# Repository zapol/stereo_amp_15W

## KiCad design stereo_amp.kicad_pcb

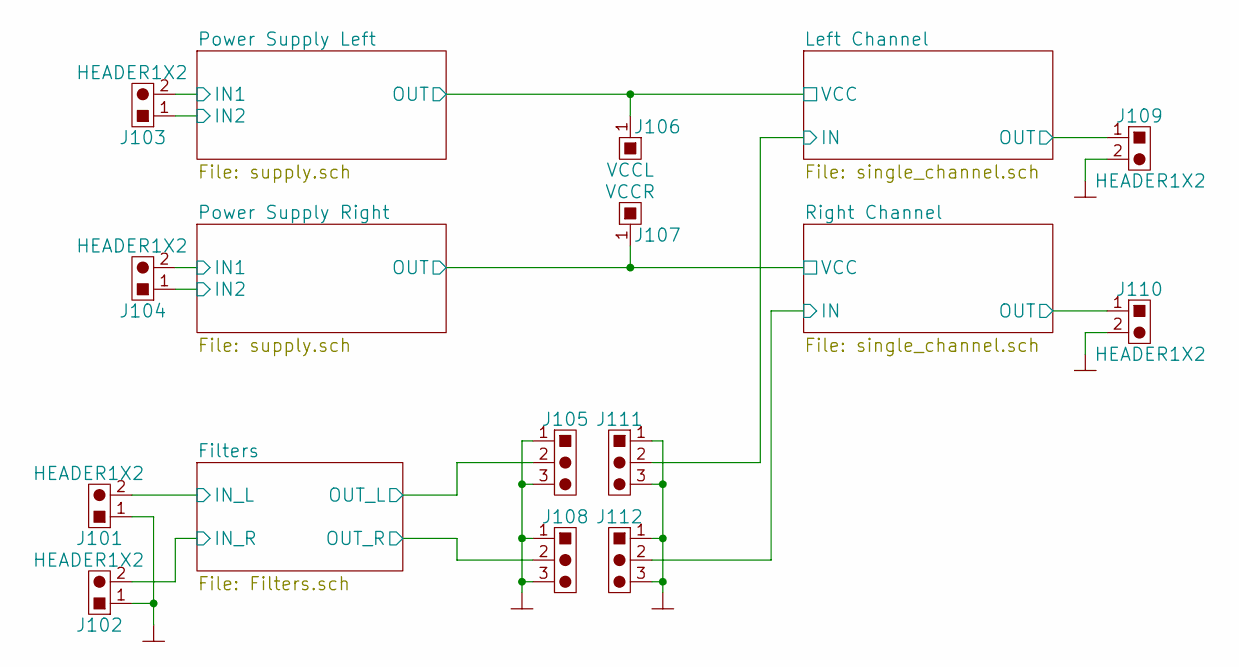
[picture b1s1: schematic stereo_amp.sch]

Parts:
J101, J102: HEADER1X2; HEADER1x2V
J103, J104, J109, J110: HEADER1X2; STL1550%2f2-GH
J105, J108, J111, J112: HEADER1X3; HEADER1x3V
J106: VCCL; MountHole_D4P6
J107: VCCR; MountHole_D4P6

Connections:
/Filters/IN_L: J101.2; also elsewhere on the board
/Filters/IN_R: J102.2; also elsewhere on the board
/Filters/OUT_L: J105.2; also elsewhere on the board
/Filters/OUT_R: J108.2; also elsewhere on the board
/Left Channel/IN: J111.2; also elsewhere on the board
/Left Channel/OUT: J109.1; also elsewhere on the board
/Power Supply Left/IN1: J103.2; also elsewhere on the board
/Power Supply Left/IN2: J103.1; also elsewhere on the board
/Power Supply Left/OUT: J106.1; also elsewhere on the board
/Power Supply Right/IN1: J104.2; also elsewhere on the board
/Power Supply Right/IN2: J104.1; also elsewhere on the board
/Power Supply Right/OUT: J107.1; also elsewhere on the board
/Right Channel/IN: J112.2; also elsewhere on the board
/Right Channel/OUT: J110.1; also elsewhere on the board
GND: J101.1, J102.1, J105.1, J105.3, J108.1, J108.3, J109.2, J110.2, J111.1, J111.3, J112.1, J112.3; also elsewhere on the board

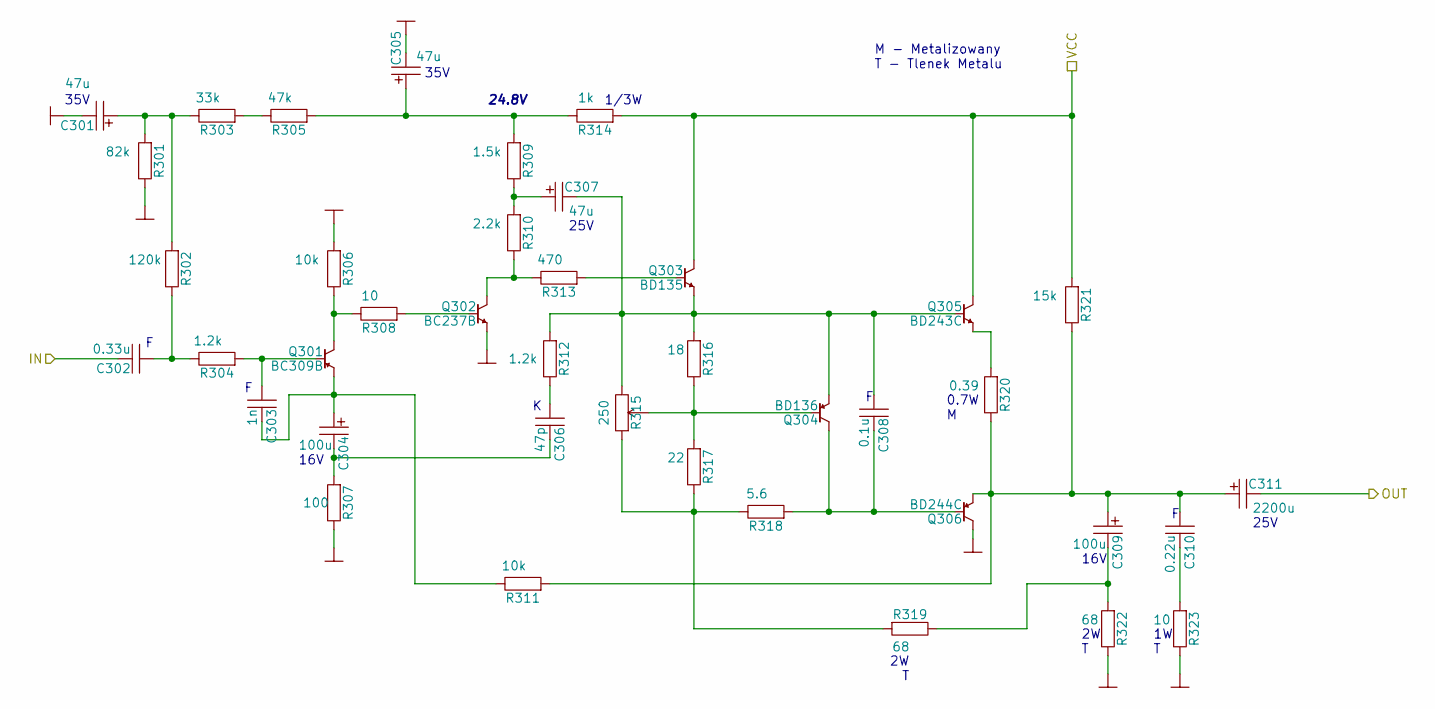
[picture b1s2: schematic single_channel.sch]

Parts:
C201, C205, C207: 47u; CAPPR_P50D63
C202: 0.33u; CAPRR_P50W35L72
C203: 1n; CAPRR_P50W25L72
C204, C209: 100u; CAPPR_P25D50
C206: 47p; CAPRR_P30W20L40
C208: 0.1u; CAPRR_P50W25L72
C210: 0.22u; CAPRR_P50W35L72
C211: 2200u; CAPPR_P75D160
Q201: BC309B; TO92
Q202: BC237B; TO92
Q203: BD135; TO126-V
Q204: BD136; TO126-V
Q205: BD243C; TO220-V
Q206: BD244C; TO220-V
R201: 82k; R0805
R202: 120k; R0805
R203: 33k; R0805
R204, R212: 1.2k; R0805
R205: 47k; R0805
R206, R211: 10k; R0805
R207: 100; R0805
R208: 10; R0805
R209: 1.5k; R0805
R210: 2.2k; R0805
R213: 470; R0805
R214: 1k; RESR_D40P50
R215: 250; POT-3339P
R216: 18; R0805
R217: 22; R0805
R218: 5.6; R0805
R219: 68; RESR_D40P50
R220: 0.39; RESA_D30L90
R221: 15k; R0805
R222: 68; RESR_D40P40
R223: 10; RESR_D30P40

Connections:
/Left Channel/IN: C202.2; also elsewhere on the board
/Left Channel/OUT: C211.2; also elsewhere on the board
/Power Supply Left/OUT: Q203.2 (C), Q205.2 (C), R214.1, R221.1; also elsewhere on the board
GND: C201.2, C205.2, Q202.3 (E), Q206.2 (C), R201.2, R206.1, R207.2, R222.2, R223.2; also elsewhere on the board
unnamed: C201.1, R201.1, R202.1, R203.2
unnamed: C202.1, R202.2, R204.2
unnamed: C203.1, Q201.2 (B), R204.1
unnamed: C203.2, C204.1, Q201.3 (E), R211.2
unnamed: C204.2, C206.2, R207.1
unnamed: C205.1, R205.1, R209.1, R214.2
unnamed: C206.1, R212.2
unnamed: C207.1, R209.2, R210.1
unnamed: C207.2, C208.1, Q203.1 (E), Q204.1 (E), Q205.1 (B), R212.1, R215.3, R216.1
unnamed: C208.2, Q204.2 (C), Q206.1 (B), R218.1
unnamed: C209.1, C210.1, C211.1, Q206.3 (E), R211.1, R220.2, R221.2
unnamed: C209.2, R219.2, R222.1
unnamed: C210.2, R223.1
unnamed: Q201.1 (C), R206.2, R208.2
unnamed: Q202.1 (C), R210.2, R213.2
unnamed: Q202.2 (B), R208.1
unnamed: Q203.3 (B), R213.1
unnamed: Q204.3 (B), R215.2, R216.2, R217.1
unnamed: Q205.3 (E), R220.1
unnamed: R203.1, R205.2
unnamed: R215.1, R217.2, R218.2, R219.1

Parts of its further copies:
C301, C305, C307: 47u; CAPPR_P50D63
C302: 0.33u; CAPRR_P50W35L72
C303: 1n; CAPRR_P50W25L72
C304, C309: 100u; CAPPR_P25D50
C306: 47p; CAPRR_P30W20L40
C308: 0.1u; CAPRR_P50W25L72
C310: 0.22u; CAPRR_P50W35L72
C311: 2200u; CAPPR_P75D160
Q301: BC309B; TO92
Q302: BC237B; TO92
Q303: BD135; TO126-V
Q304: BD136; TO126-V
Q305: BD243C; TO220-V
Q306: BD244C; TO220-V
R301: 82k; R0805
R302: 120k; R0805
R303: 33k; R0805
R304, R312: 1.2k; R0805
R305: 47k; R0805
R306, R311: 10k; R0805
R307: 100; R0805
R308: 10; R0805
R309: 1.5k; R0805
R310: 2.2k; R0805
R313: 470; R0805
R314: 1k; RESR_D40P50
R315: 250; POT-3339P
R316: 18; R0805
R317: 22; R0805
R318: 5.6; R0805
R319: 68; RESR_D40P50
R320: 0.39; RESA_D30L90
R321: 15k; R0805
R322: 68; RESR_D40P40
R323: 10; RESR_D30P40

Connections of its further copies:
/Power Supply Right/OUT: Q303.2 (C), Q305.2 (C), R314.1, R321.1; also elsewhere on the board
/Right Channel/IN: C302.2; also elsewhere on the board
/Right Channel/OUT: C311.2; also elsewhere on the board
GND: C301.2, C305.2, Q302.3 (E), Q306.2 (C), R301.2, R306.1, R307.2, R322.2, R323.2; also elsewhere on the board
unnamed: C301.1, R301.1, R302.1, R303.2
unnamed: C302.1, R302.2, R304.2
unnamed: C303.1, Q301.2 (B), R304.1
unnamed: C303.2, C304.1, Q301.3 (E), R311.2
unnamed: C304.2, C306.2, R307.1
unnamed: C305.1, R305.1, R309.1, R314.2
unnamed: C306.1, R312.2
unnamed: C307.1, R309.2, R310.1
unnamed: C307.2, C308.1, Q303.1 (E), Q304.1 (E), Q305.1 (B), R312.1, R315.3, R316.1
unnamed: C308.2, Q304.2 (C), Q306.1 (B), R318.1
unnamed: C309.1, C310.1, C311.1, Q306.3 (E), R311.1, R320.2, R321.2
unnamed: C309.2, R319.2, R322.1
unnamed: C310.2, R323.1
unnamed: Q301.1 (C), R306.2, R308.2
unnamed: Q302.1 (C), R310.2, R313.2
unnamed: Q302.2 (B), R308.1
unnamed: Q303.3 (B), R313.1
unnamed: Q304.3 (B), R315.2, R316.2, R317.1
unnamed: Q305.3 (E), R320.1
unnamed: R303.1, R305.2
unnamed: R315.1, R317.2, R318.2, R319.1

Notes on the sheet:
0.7W M
M - Metalizowany T - Tlenek Metalu
1W T
16V
2W T
25V
1/3W
35V
24.8V

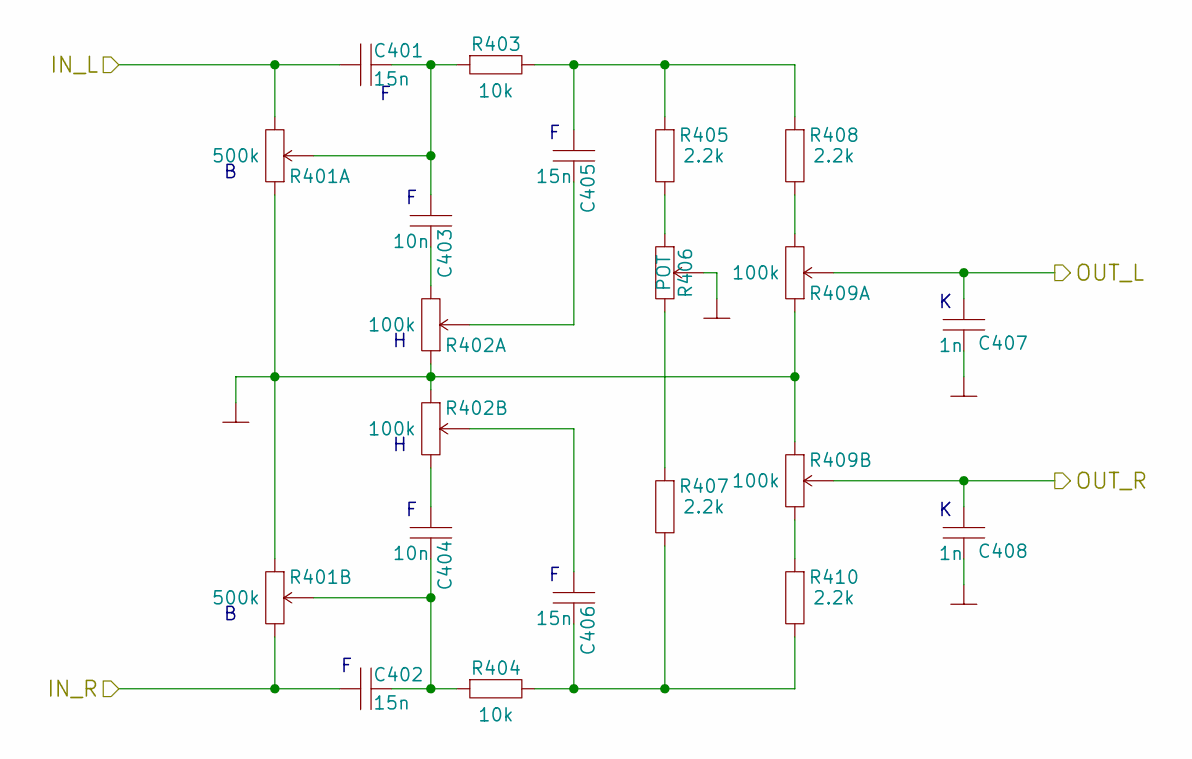
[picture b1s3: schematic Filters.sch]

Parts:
C401, C402, C405, C406: 15n; CAPRR_P50W25L72
C403, C404: 10n; CAPRR_P50W25L72
C407, C408: 1n; C0805
R401: 500k; POT_AUDIO_R6_DUAL_H
R402, R409: 100k; POT_AUDIO_R6_DUAL_H
R403, R404: 10k; RESA_D20L40
R405, R407, R408, R410: 2.2k; RESA_D20L40
R406: POT; POT_AUDIO_R6_H

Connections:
/Filters/IN_L: C401.1, R401.3; also elsewhere on the board
/Filters/IN_R: C402.1, R401.6 (3); also elsewhere on the board
/Filters/OUT_L: C407.1, R409.2; also elsewhere on the board
/Filters/OUT_R: C408.1, R409.5 (2); also elsewhere on the board
GND: C407.2, C408.2, R401.1, R401.4 (1), R402.1, R402.4 (1), R406.2, R409.1, R409.4 (1); also elsewhere on the board
unnamed: C401.2, C403.1, R401.2, R403.1
unnamed: C402.2, C404.2, R401.5 (2), R404.1
unnamed: C403.2, R402.3
unnamed: C404.1, R402.6 (3)
unnamed: C405.1, R403.2, R405.1, R408.1
unnamed: C405.2, R402.2
unnamed: C406.1, R402.5 (2)
unnamed: C406.2, R404.2, R407.2, R410.2
unnamed: R405.2, R406.1
unnamed: R406.3, R407.1
unnamed: R408.2, R409.3
unnamed: R409.6 (3), R410.1

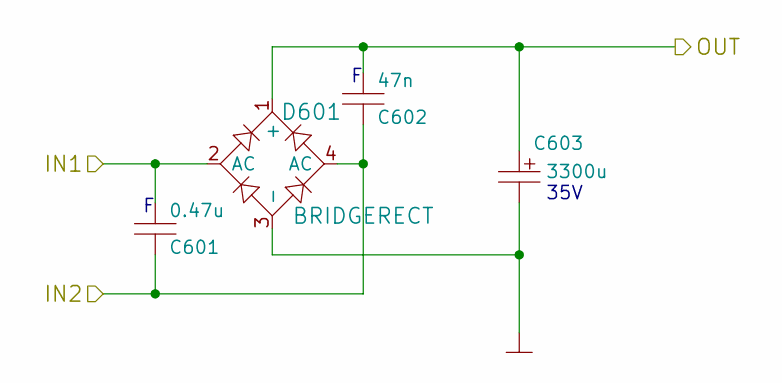
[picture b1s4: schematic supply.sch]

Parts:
C501: 0.47u; CAPRR_P50W50L72
C502: 47n; CAPRR_P50W25L72
C503: 3300u; CAPPR_P75D180
D501: BRIDGERECT; KBPC606

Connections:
/Power Supply Left/IN1: C501.1, D501.2 (AC); also elsewhere on the board
/Power Supply Left/IN2: C501.2, C502.2, D501.4 (AC); also elsewhere on the board
/Power Supply Left/OUT: C502.1, C503.1, D501.1 (+); also elsewhere on the board
GND: C503.2, D501.3 (-); also elsewhere on the board

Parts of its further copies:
C601: 0.47u; CAPRR_P50W50L72
C602: 47n; CAPRR_P50W25L72
C603: 3300u; CAPPR_P75D180
D601: BRIDGERECT; KBPC606

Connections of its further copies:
/Power Supply Right/IN1: C601.1, D601.2 (AC); also elsewhere on the board
/Power Supply Right/IN2: C601.2, C602.2, D601.4 (AC); also elsewhere on the board
/Power Supply Right/OUT: C602.1, C603.1, D601.1 (+); also elsewhere on the board
GND: C603.2, D601.3 (-); also elsewhere on the board

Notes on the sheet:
35V

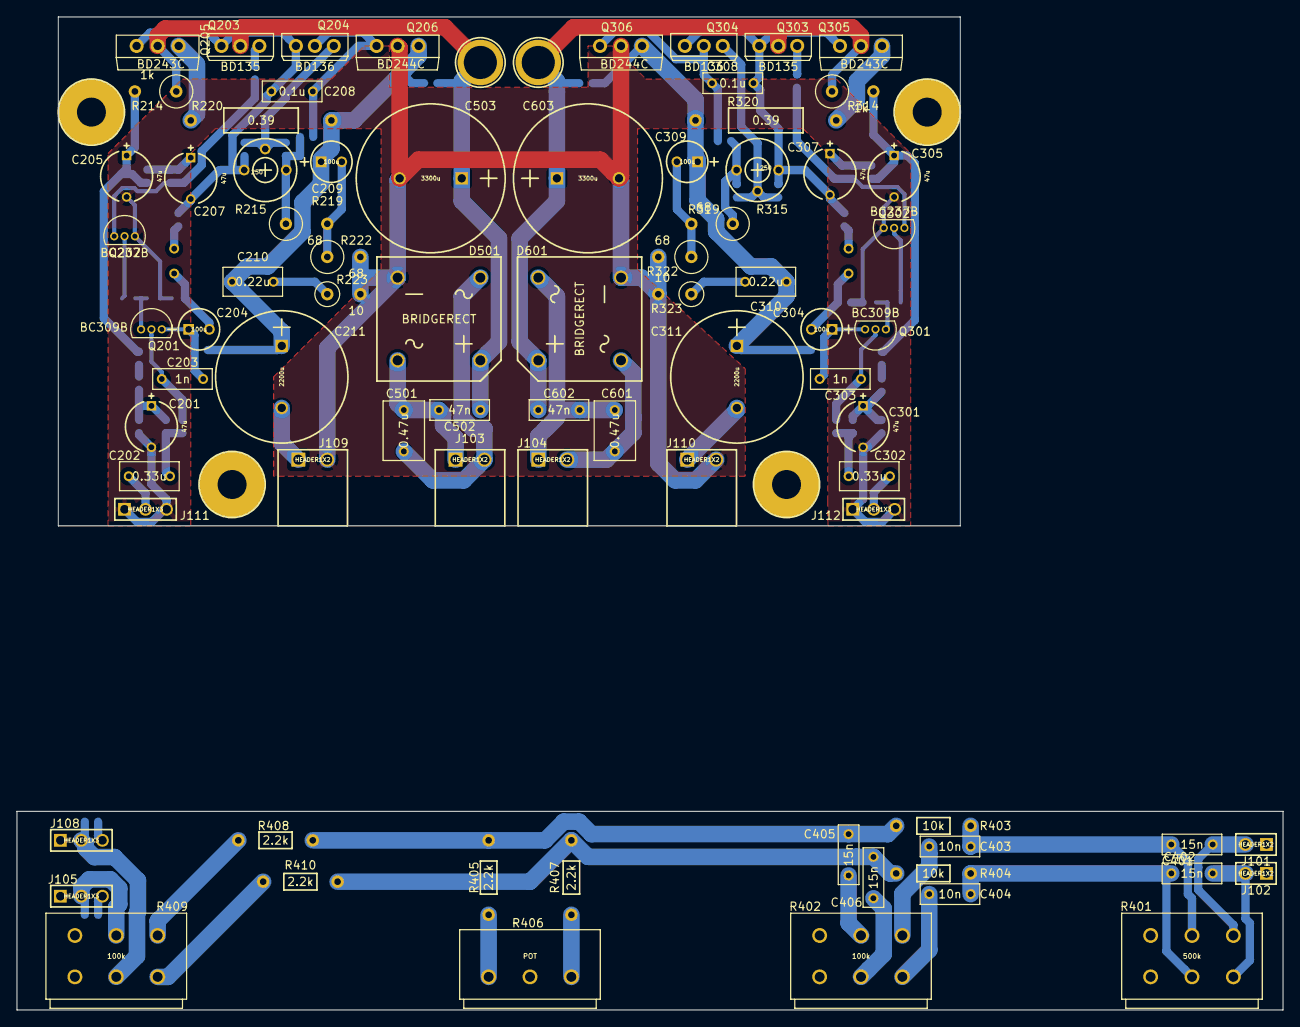
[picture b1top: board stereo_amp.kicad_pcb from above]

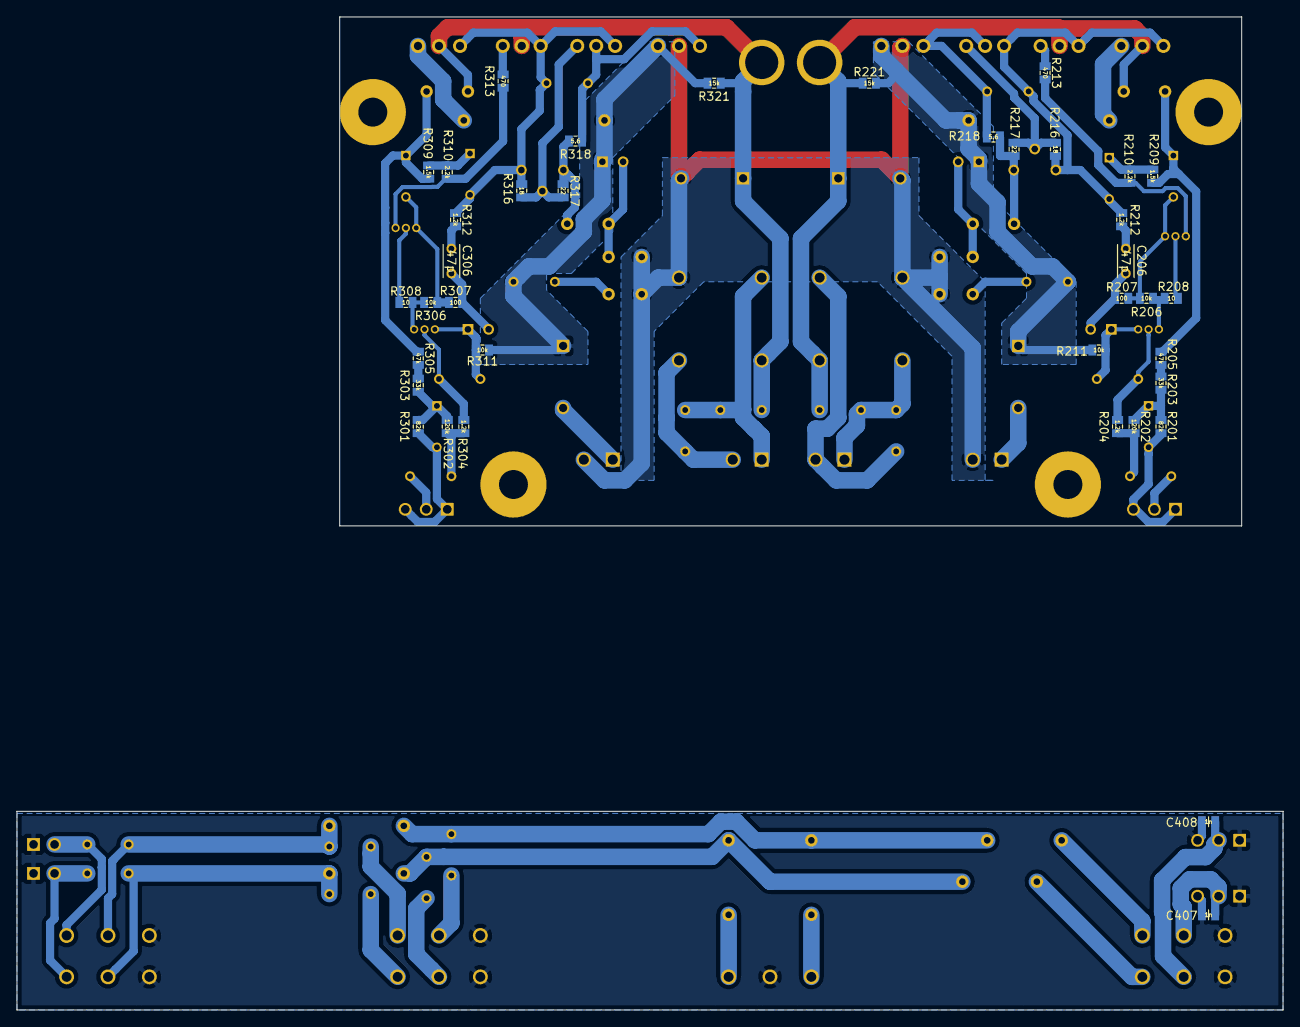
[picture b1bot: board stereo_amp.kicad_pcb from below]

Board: 2 copper layers, 153.0 x 120.0 mm, 122 parts (38 on the bottom side), 69 nets.

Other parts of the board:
MountHole_D35P80, MountHole_D35P80#2, MountHole_D35P80#3, MountHole_D35P80#4: VAL**; MountHole_D35P80

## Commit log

2014-10-23 Initial commit. Schematic completed, footprints created, started routing.
2014-10-26 Finished placement and routing.
2014-10-27 Fixed transistors with swapped E-C
2014-10-28 Updated PCB layout to reflect changes in footprints.
2014-10-29 Turned all power transistors around. Resized filter board to fit knobs.
2014-10-30 Added blender model of amplifier.
2014-10-31 More details added to blender model
